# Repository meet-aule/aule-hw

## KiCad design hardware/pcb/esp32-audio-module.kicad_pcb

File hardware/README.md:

# Hardware

Everything physical in Aule: the board, its fabrication package, its 3D model and the desk dock that holds the e-ink panel.

> **Prototype v0.2.2.** The design passes its electrical and design-rule checks, but the first boards have not been brought up yet. Treat it as a reference, not a kit, until they are.

## Folder layout

```text
pcb/          KiCad 10 project of the board (schematic in four sheets, layout, project libraries)
fab/          JLCPCB package: Gerbers, drill files, BOM.csv and CPL.csv
board/        STEP model of the assembled board, with every part, and a render
enclosure/    Desk dock: build123d source, STEP and STL of each part, renders and print settings
ordering/     How to check JLCPCB's placement preview, part by part, before paying
```

## Board (`pcb/`)

- 92 × 48 mm, 4 layers, 147 parts, all orderable from LCSC.
- Open `pcb/esp32-audio-module.kicad_pro` with **KiCad 10**. Project-specific symbols and footprints are in `pcb/heypcb-libs/`; everything else comes from KiCad's standard libraries.
- Sheets:
  - `mcu`: ESP32-S3 module, LIS2DH12 accelerometer, talk button, touch connector (J6), programming pads.
  - `audio`: ES7210 microphone ADC, ES8311 codec, PAM8302A amplifier, two MEMS microphones, speaker connector, microphone mute switch.
  - `power`: BQ24075 charger with power path, TPS63000 buck-boost, battery thermal cut-off, USB protection, power switch, battery connector.
  - `connectors`: USB-C, e-ink panel connector (J5) and its high-voltage booster.
- **Microphone mute is pure hardware.** The slide switch cuts the microphones' bias supply and the green "mic on" LED with it; the firmware cannot turn either back on.
- Checks for this revision: DRC with the project rules, **0 errors** ([`pcb/drc.json`](pcb/drc.json)); ERC, **0 errors** ([`pcb/erc.json`](pcb/erc.json)). DRC warnings are silkscreen overlaps and footprint library-version mismatches; ERC warnings are pin-type notices.
- What changed in v0.2.2: only L2, the inductor of the e-ink high-voltage booster, from 68 µH to 10 µH (Sunlord SWPA6045S100MT, C79272), as the UC8179 panel controller requires.

**Not measured yet:** the high-voltage booster with the new inductor, the real panel and touch flex positions, and touch sensing through the optional lens.

## Fabrication (`fab/`)

The files of our first order (12 November 2026), with one change since: the silkscreen text now says «aule». The files exactly as ordered are at commit [`68c8f9a`](https://github.com/meet-aule/aule-hw/tree/68c8f9a/hardware/fab). Upload the Gerber files as a ZIP, then `BOM.csv` and `CPL.csv` for assembly. `CPL-rotations.txt` explains where each rotation comes from. Read [`ordering/`](ordering/README.md) before confirming the order: the placement preview is the one check that cannot be done from the files.

## Enclosure (`enclosure/`)

A folding desk dock (194 × 138.5 mm) in seven printed parts, about 13.5 hours and 387 g of PETG. The source is parametric ([build123d](https://github.com/gumyr/build123d)) and checks itself: `dock.py` runs 635 fit checks against the board model in `board/`, and `printcheck.py` checks every printed layer for overhangs. Details, print settings, hardware list and assembly in [`enclosure/README.md`](enclosure/README.md).

## Firmware pin map

The pins the firmware needs are in [`../software/`](../software/).

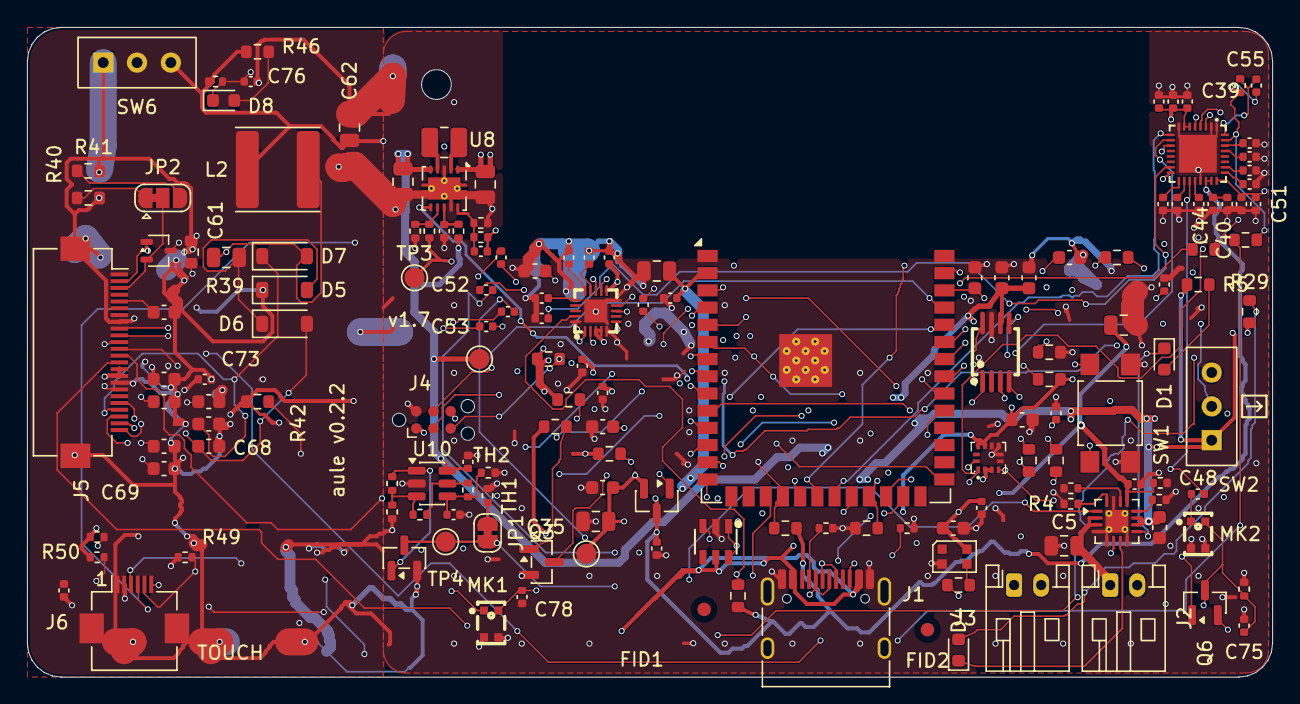
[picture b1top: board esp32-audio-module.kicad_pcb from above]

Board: 4 copper layers, 92.0 x 48.0 mm, 157 parts (0 on the bottom side), 103 nets.

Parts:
C1, C11, C12, C36, C37: 100nF; C_0603_1608Metric
C2, C5: 10uF; C_0805_2012Metric
C4, C62: 4.7uF; C_0805_2012Metric
C6, C7, C13, C72: 1uF; C_0603_1608Metric
C14, C15, C16, C28, C32, C33, C38, C39, C40, C51, C58, C59, C73, C75, C77: 100nF; C_0402_1005Metric
C17, C18, C19, C20, C21, C22, C24, C25, C41, C42, C43, C44, C45, C46, C47, C48, C49, C50, C52, C53, C54: 1uF; C_0402_1005Metric
C27: 10uF 25V; C_0805_2012Metric
C29, C30: 1nF; C_0402_1005Metric
C31, C35: 47uF; C_0805_2012Metric
C34: 10uF; C_0603_1608Metric
C55, C76: 10nF; C_0402_1005Metric
C56: 2.2uF 25V; C_0402_1005Metric
C57: 10uF 25V; C_0603_1608Metric
C60: 39pF; C_0402_1005Metric
C61: 4.7uF 50V; C_0805_2012Metric
C64, C65, C67, C68, C69, C70, C71: 1uF 50V; C_0603_1608Metric
C78: 10nF 25V C0G; C_0402_1005Metric
D1: red LED; LED_0603_1608Metric
D2: WS2812B-2020 RGB; LED_WS2812B-2020_PLCC4_2.0x2.0mm
D4: green LED; LED_0603_1608Metric
D5, D6, D7: MBR0530; D_SOD-123
D8: green LED mic on; LED_0603_1608Metric
FID1, FID2: FID; Fiducial_1mm_Mask2mm
H1: MountingHole M2; MountingHole_2.2mm_M2
J1: USB-C; USB_C_Receptacle_HRO_TYPE-C-31-M-12
J2: BATT; JST_PH_S2B-PH-K_1x02_P2.00mm_Horizontal
J3: SPEAKER; JST_PH_S2B-PH-K_1x02_P2.00mm_Horizontal
J4: TC2030-NL prog pads; Tag-Connect_TC2030-IDC-NL_2x03_P1.27mm_Vertical
J5: EPD 24P FPC (GDEY075T7); Hirose_FH12-24S-0.5SH_1x24-1MP_P0.50mm_Horizontal
J6: TOUCH 6P FPC (GT911); Hirose_FH12-6S-0.5SH_1x06-1MP_P0.50mm_Horizontal
JP1: TH1 (cortar para NTC externo); SolderJumper-2_P1.3mm_Bridged_RoundedPad1.0x1.5mm
JP2: RESE 0.47R=7.5in / 3R=4.2in; SolderJumper-3_P1.3mm_Bridged12_RoundedPad1.0x1.5mm
L1: 2.2uH; L_1008_2520Metric
L2: 10uH; L_Sunlord_SWPA6045S
MK1, MK2: ZTS6216; MIC-SMD_4P-L2.8-W1.9-P1.84-TL
Q1: SI2301CDS; SOT95P237X102-3N
Q3, Q4: 2N7002; SOT-23
Q5: Si1308EDL; SOT-323_SC-70
Q6: SI2301CDS mic bias switch; SOT95P237X102-3N
R1, R8, R39, R42: 10k; R_0603_1608Metric
R2, R3: 5.1k; R_0402_1005Metric
R4: 3.9k; R_0402_1005Metric
R5, R29: 1k; R_0603_1608Metric
R9, R10, R14, R19, R20, R21: 100k; R_0603_1608Metric
R12, R13: 30k; R_0603_1608Metric
R15, R16: 4.7k; R_0603_1608Metric
R17: 56k; R_0402_1005Metric
R18: 9.76k; R_0402_1005Metric
R22: 330R; R_0603_1608Metric
R23, R24: 27k; R_0603_1608Metric
R25: 3.3k; R_0402_1005Metric
R28, R33, R34, R37, R38, R48: 100k; R_0402_1005Metric
R30: 1.5k; R_0402_1005Metric
R31: 68k; R_0402_1005Metric
R32: 49.9k; R_0402_1005Metric
R35: 100R; R_0402_1005Metric
R36: 3.3M; R_0402_1005Metric
R40: 0.47R; R_0603_1608Metric
R41: 3R; R_0603_1608Metric
R46: 2.2k; R_0603_1608Metric
R47: 1M; R_0402_1005Metric
R49, R50: 4.7k; R_0402_1005Metric
R51: 10k; R_0402_1005Metric
SW1: TL3305AF160QG; SW_SPST_TL3305A
SW2: SS12D00G6 system enable; SW_Slide_SPDT_YIZHI_SS12D00G6_P2.50mm
SW6: SS12D00G6 mic mute; SW_Slide_SPDT_YIZHI_SS12D00G6_P2.50mm
TH1: 10k B4250; R_0402_1005Metric
TH2: 100k B4250 1%; R_0402_1005Metric
TP1: 3V3; TestPoint_Pad_D1.5mm
TP2: VSYS; TestPoint_Pad_D1.5mm
TP3: AUDIO_3V3; TestPoint_Pad_D1.5mm
TP4: TS; TestPoint_Pad_D1.5mm
U1: ESP32-S3-WROOM-1-N16R8; ESP32-S3-WROOM-1
U2: BQ24075; VQFN-16-1EP_3x3mm_P0.5mm_EP1.68x1.68mm_ThermalVias
U4: ES8311; WQFN-20_L3.0-W3.0-P0.40-BL-EP1.7
U5: USBLC6-2SC6; SOT-23-6_L2.9-W1.6-P0.95-LS2.8-BL
U6: PAM8302AASCR; MSOP-8_L3.0-W3.0-P0.65-LS5.0-BL
U7: LIS2DH12TR; LGA-12_L2.0-W2.0-P0.50-BL
U8: TPS63000 buck-boost 3.45V; Texas_DRC0010J_ThermalVias
U9: ES7210 4ch ADC; QFN-32_L4.0-W4.0-P0.40-BL-EP2.7
U10: MCP65R41-1202 corte térmico; SOT-23-6

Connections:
3V3: C1.1, C2.1, C7.1, C31.1, C32.1, C33.1, C35.1, C37.1, C60.1, C62.1, C72.1, C73.1, C77.1, D2.4, J4.1, J5.15, J5.16, J6.2, L2.1, Q1.2 (S), R1.1, R8.1, R17.1, R19.1, R21.2, R42.1, R46.1, R48.1, R49.1, R50.1, R51.1, SW6.3, TP1.1, U1.2 (3V3), U7.2 (CS), U7.3 (SDO/SA0), U7.9 (VDD), U7.10 (VDD_IO), U8.1
ACC_INT1: U1.10 (IO17), U7.12 (INT1)
AEC_REF_N: C55.2, R24.2, R25.2, U9.32
AEC_REF_N_AC: C53.2, R24.1
AEC_REF_P: C55.1, R23.2, R25.1, U9.31
AEC_REF_P_AC: C52.2, R23.1
AMP_INN: R13.2, U6.4 (IN-)
AMP_INN_AC: C25.2, R13.1
AMP_INP: R12.2, U6.3 (IN+)
AMP_INP_AC: C24.2, R12.1
AUDIO_3V3: C14.1, C15.1, C16.1, C17.1, C38.1, C39.1, C40.1, C41.1, C42.1, Q1.3 (D), R15.1, R16.1, R37.1, TP3.1, U4.3 (PVDD), U4.4 (DVDD), U4.11 (AVDD), U9.6, U9.7, U9.22, U9.23
AUDIO_PWR_N: Q1.1 (G), R19.2, U1.12 (IO8)
BAT_RAW: C5.1, J2.1, U2.2, U2.3
CHG_DONE_LED_A: D4.2, R29.2
CHG_HOT: Q4.1, R36.2, U10.1
CHG_ILIM: R30.1, U2.12
CHG_ISET: R4.1, U2.16
CHG_PGOOD: D4.1, U2.7
CHG_TEMP: JP1.1, Q4.3, TP4.1, U2.1
CHG_TMR: R31.1, U2.14
CMP_NTC: C58.1, R32.2, TH2.1, U10.4
CMP_REF: R32.1, R33.1, U10.5
CMP_TH: R33.2, R34.1, R36.1, U10.3
DAC_OUTN: C25.1, C53.1, U4.13 (OUTN)
DAC_OUTP: C24.1, C52.1, U4.12 (OUTP)
EPD_BUSY: J5.9, U1.32 (IO39)
EPD_CS: J5.12, R42.2, U1.22 (IO14)
EPD_DC: J5.11, U1.24 (IO47)
EPD_GDR: J5.2, Q5.1, R39.1
EPD_MOSI: J5.14, U1.17 (IO9)
EPD_PREVGH: C68.1, D7.1, J5.21
EPD_PREVGL: C70.1, D6.2, J5.23
EPD_PUMP: C61.2, D5.2, D6.1
EPD_RESE: J5.3, JP2.2, Q5.2
EPD_RESE_3R: JP2.3, R41.1
EPD_RESE_047: JP2.1, R40.1
EPD_RST: J5.10, U1.25 (IO48)
EPD_SCK: J5.13, U1.7 (IO7)
EPD_SW: C61.1, D7.2, L2.2, Q5.3
EPD_VCOM: C71.1, J5.24
EPD_VDD: C65.1, J5.18
EPD_VGH: C64.1, J5.5
EPD_VSH: C67.1, J5.20
EPD_VSL: C69.1, J5.22
GND: C1.2, C2.2, C4.2, C5.2, C6.2, C7.2, C11.2, C12.2, C13.2, C14.2, C15.2, C16.2, C17.2, C18.2, C19.2, C20.2, C22.2, C27.2, C28.2, C29.2, C30.2, C31.2, C32.2, C33.2, C34.2, C35.2, C36.2, C37.2, C38.2, C39.2, C40.2, C41.2, C42.2, C43.2, C44.2, C45.2, C46.2, C47.2, C49.2, C50.2, C51.2, C54.2, C56.2, C57.2, C58.2, C59.2, C62.2, C64.2, C65.2, C67.2, C68.2, C69.2, C70.2, C71.2, C72.2, C73.2, C75.2, C76.2, C77.2, C78.2, D2.2, D5.1, J1.A1 (GND), J1.A12 (GND), J1.B1 (GND), J1.B12 (GND), J1.SH (SHIELD), J2.2, J4.2, J5.8, J5.17, J5.MP, J6.1, J6.MP, MK1.2 (GND), MK1.3 (GND), MK2.2, MK2.3, Q3.2, Q4.2, R2.2, R3.2, R4.2, R10.2, R14.2, R18.2, R28.2, R30.2, R31.2, R34.2, R38.2, R39.2, R40.2, R41.2, R47.2, SW1.2, SW2.3 (B), SW6.1, TH1.2, TH2.2, U1.1 (GND), U1.40 (GND), U1.41 (GND), U2.4, U2.5, U2.8, U2.15, U2.17, U4.5 (DGND), U4.10 (AGND), U4.20 (CE), U4.21 (EP), U5.2 (GND), U6.7 (GND), U7.5 (RES), U7.6 (GND), U7.7 (GND), U7.8 (GND), U8.3, U8.9, U8.11, U9.1, U9.2, U9.8, U9.21, U9.33, U10.2
I2C_SCL: R15.2, U1.18 (IO10), U4.1 (CCLK), U7.1 (SCL/SPC), U9.4
I2C_SDA: R16.2, U1.19 (IO11), U4.19 (CDATA), U7.4 (SDA/SDI/SDO), U9.3
I2S_BCLK: U1.21 (IO13), U4.6 (SCLK/DMIC_SCL), U9.9
I2S_DIN: U1.8 (IO15), U9.11
I2S_DOUT: U1.9 (IO16), U4.9 (DSDIN)
I2S_LRCLK: U1.4 (IO4), U4.8 (LRCK), U9.10
I2S_MCLK: U1.20 (IO12), U4.2 (MCLK), U9.5
IO0_BOOT: J4.6, U1.27 (IO0)
J1_CC1: J1.A5 (CC1), R2.1
J1_CC2: J1.B5 (CC2), R3.1
J1_USB_DM: J1.A7 (D-), J1.B7 (D-), U1.13 (USB_D-), U5.1 (I/O1), U5.6 (I/O1)
J1_USB_DP: J1.A6 (D+), J1.B6 (D+), U1.14 (USB_D+), U5.3 (I/O2)
MIC1N: C22.1, U9.15
MIC1P: C21.2, U9.16
MIC2N: C49.1, U9.20
MIC2P: C48.2, U9.19
MIC2_OUT: C48.1, MK2.1
MICBIAS12: C50.1, C51.1, Q6.2, U9.24
MICBIAS34: C54.1, U9.26
MIC_EN_N: C76.1, D8.1, Q6.1, R48.2, SW6.2, U1.6 (IO6)
MIC_LED_A: D8.2, R46.2
MIC_OUT: C21.1, MK1.1 (OUT)
MIC_VDD: C75.1, C78.1, MK1.4 (VDD), MK2.4, Q6.3, R47.1
PA_EN: R14.1, U1.23 (IO21), U6.1 (~SD)
PWR_EN: R9.1, SW2.2 (COM), U8.6
R9_VBAT_SENSE: C12.1, R9.2, R10.1, U1.39 (IO1)
RGB_DATA: R22.1, U1.31 (IO38)
RGB_DIN: D2.3, R22.2
SPK_N: C30.1, J3.2, U6.8 (VO-)
SPK_P: C29.1, J3.1, U6.5 (VO+)
SW1_BTN_SIG: C11.1, R8.2, SW1.1, U1.38 (IO2)
TH1_NTC: JP1.2, TH1.1
TOUCH_INT: J6.4, U1.5 (IO5)
TOUCH_RST: J6.3, R51.2, U1.35 (IO42)
TOUCH_SCL: J6.6, R50.2, U1.33 (IO40)
TOUCH_SDA: J6.5, R49.2, U1.34 (IO41)
U1_EN: C13.1, J4.5, R1.2, U1.3 (EN)
U2_CHG_LED_A: D1.2 (A), R5.2
U2_STAT: D1.1 (K), U2.9
U4_ADCVREF: C19.1, U4.15 (ADCVREF)
U4_DACVREF: C18.1, U4.14 (DACVREF)
U4_VMID: C20.1, U4.16 (VMID)
U8_FB: C60.2, R17.2, R18.1, U8.10
U8_L1: L1.1, U8.4
U8_L2: L1.2, U8.2
U8_PS: R37.2, R38.1, U8.7
U8_VINA: C28.1, R35.2, U8.8
U9_REFP12: C43.1, U9.17
U9_REFP34: C46.1, U9.29
U9_REFQ12: C44.1, U9.18
U9_REFQ34: C47.1, U9.30
U9_REFQM: C45.1, U9.25
UART_RXD0: J4.3, U1.36 (RXD0)
UART_TXD0: J4.4, U1.37 (TXD0)
USB_DET_GATE: Q3.1, R20.2
VBUS: C4.1, C56.1, J1.A4 (VBUS), J1.A9 (VBUS), J1.B4 (VBUS), J1.B9 (VBUS), R20.1, R28.1, U2.13, U5.5 (VBUS)
VBUS_SENSE: C36.1, Q3.3, R21.1, U1.11 (IO18)
VSYS: C6.1, C27.1, C34.1, C57.1, C59.1, R5.1, R29.1, R35.1, SW2.1 (A), TP2.1, U2.6, U2.10, U2.11, U6.6 (VDD), U8.5, U10.6
